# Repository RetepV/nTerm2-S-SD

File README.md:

# nTerm2-S-SD
My rendition of the uTerm2-S. In SMD, but easily solderable. In a slightly more usable form. As extra, it can switch between normal and cross (null-modem) in software.

This is a rendition of the nTerm2-S with extra PSRAM, a few extra I/O lines, and an SD card slot.

It is based on the FABGL library from Fabrizio Di Vittori.

THIS IS A WORK IN PROGESS! I.E. UNLESS STATED AS WORKING, IT DOES NOT WORK!

This design is available under GPL License V3. This means that I DO NOT release it for commercial use, unless with my explicit written and signed consent. Please contact me if you have commercial questions.

uTerm2-S: https://hackaday.io/project/181583-uterm2-s-a-multi-emulation-color-rs232-terminal
fabgl: http://www.fabglib.org/, https://github.com/fdivitto/FabGL

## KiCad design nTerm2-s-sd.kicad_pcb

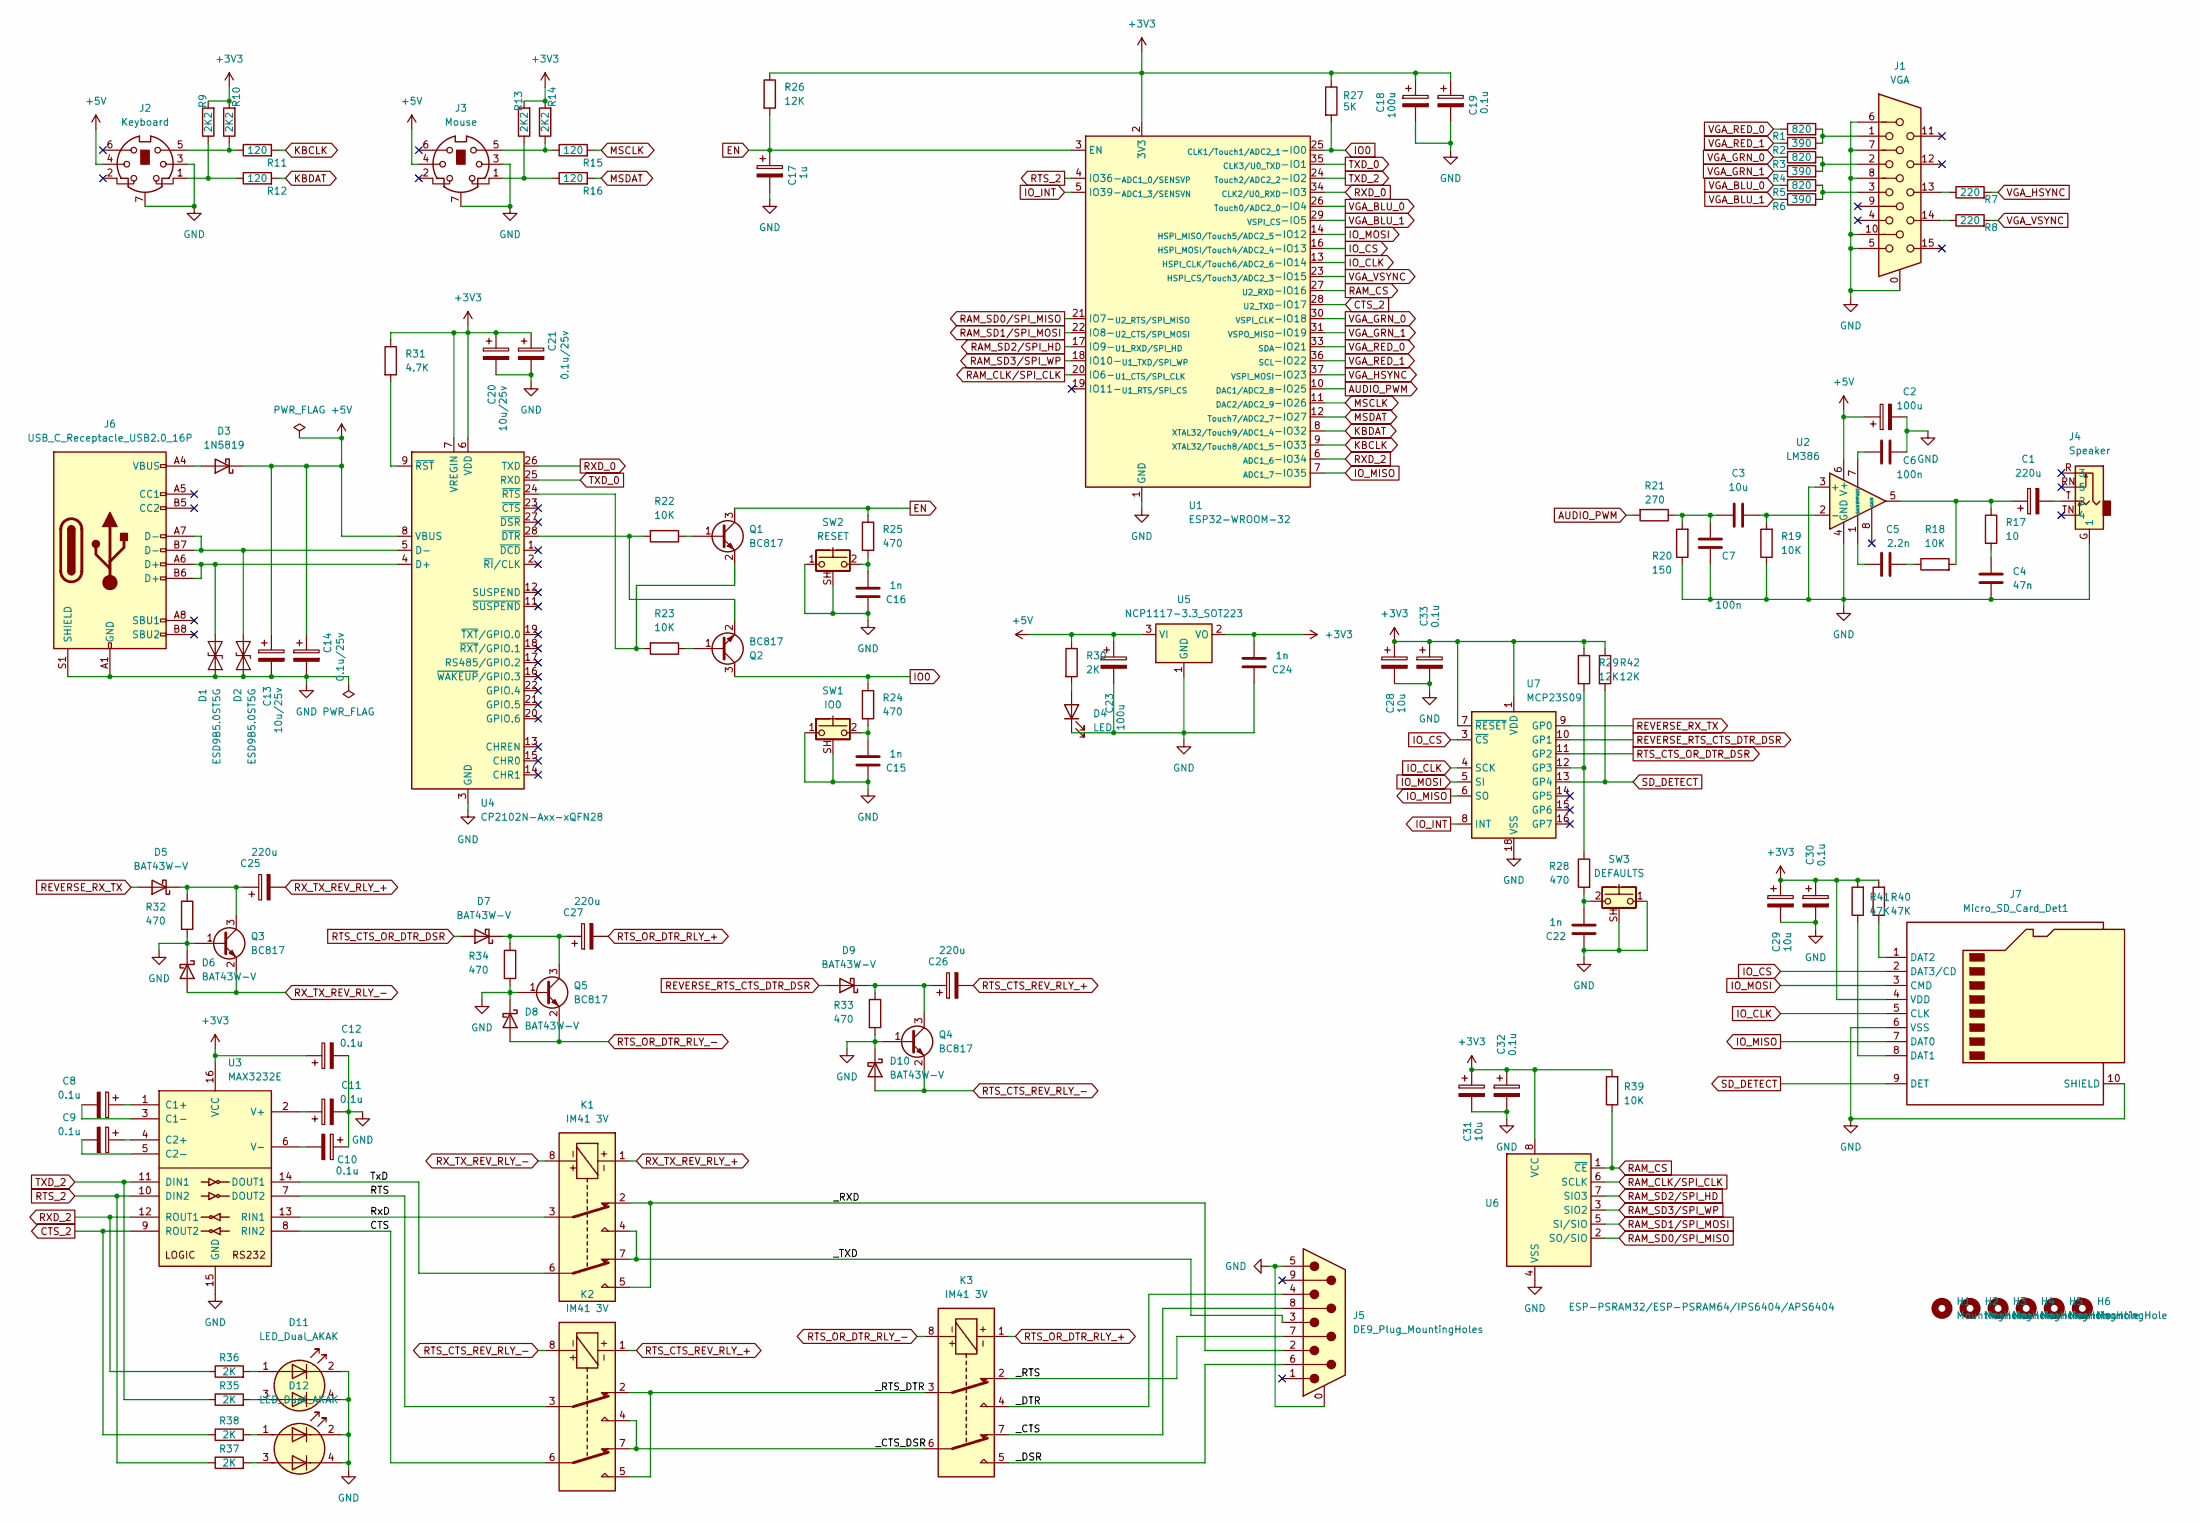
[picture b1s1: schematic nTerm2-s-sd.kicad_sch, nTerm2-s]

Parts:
C1: 220u; CP_Elec_6.3x7.7
C2: 100u; CP_Elec_6.3x7.7
C3: 10u; C_0805_2012Metric_Pad1.18x1.45mm_HandSolder
C4: 47n; C_0603_1608Metric_Pad1.08x0.95mm_HandSolder
C5: 2.2n; C_0603_1608Metric_Pad1.08x0.95mm_HandSolder
C6, C7: 100n; C_0603_1608Metric_Pad1.08x0.95mm_HandSolder
C8, C9, C10, C11, C12, C19, C30, C32, C33: 0.1u; CP_EIA-3216-18_Kemet-A_Pad1.58x1.35mm_HandSolder
C13, C20: 10u/25v; CP_EIA-3216-18_Kemet-A_Pad1.58x1.35mm_HandSolder
C14, C21: 0.1u/25v; CP_EIA-3216-18_Kemet-A_Pad1.58x1.35mm_HandSolder
C15, C16, C22, C24: 1n; C_0603_1608Metric_Pad1.08x0.95mm_HandSolder
C17: 1u; CP_EIA-3216-18_Kemet-A_Pad1.58x1.35mm_HandSolder
C18, C23: 100u; CP_EIA-3216-18_Kemet-A_Pad1.58x1.35mm_HandSolder
C25, C26, C27: 220u; CP_EIA-3216-18_Kemet-A_Pad1.58x1.35mm_HandSolder
C28, C29, C31: 10u; CP_EIA-3216-18_Kemet-A_Pad1.58x1.35mm_HandSolder
D1, D2: ESD9B5.0ST5G; D_SOD-923
D3: 1N5819; Nexperia_CFP3_SOD-123W
D4: LED; DIALIGHT_LED_3MM_SINGLE
D5, D6, D7, D8, D9, D10: BAT43W-V; D_SOD-123
D11, D12: LED_Dual_AKAK; DIALIGHT_LED_3MM_DOUBLE
H1, H2, H3, H4, H5, H6: MountingHole; MountingHole_3.2mm_M3
J1: VGA; DSUB-15-HD_Female_Horizontal_P2.29x1.98mm_EdgePinOffset8.35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
J2: Keyboard; Connector_Mini-DIN_Female_6Pin_2rows
J3: Mouse; Connector_Mini-DIN_Female_6Pin_2rows
J4: Speaker; Jack_3.5mm_Ledino_KB3SPRS_Horizontal
J5: DE9_Plug_MountingHoles; DSUB-9_Male_Horizontal_P2.77x2.84mm_EdgePinOffset4.94mm_Hou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
J6: USB_C_Receptacle_USB2.0_16P; USB_C_Receptacle_Molex_213716-0001
J7: Micro_SD_Card_Det1; GCT-MEM2055-00-190-01-A
K1, K2, K3: IM41 3V; Relay_DPDT_AXICOM_IMSeries_JLeg
Q1, Q2, Q3, Q4, Q5: BC817; SOT-23
R1, R3, R5: 820; R_0603_1608Metric_Pad0.98x0.95mm_HandSolder
R2, R4, R6: 390; R_0603_1608Metric_Pad0.98x0.95mm_HandSolder
R7, R8: 220; R_0603_1608Metric_Pad0.98x0.95mm_HandSolder
R9, R10, R13, R14: 2K2; R_0603_1608Metric_Pad0.98x0.95mm_HandSolder
R11, R12, R15, R16: 120; R_0603_1608Metric_Pad0.98x0.95mm_HandSolder
R17: 10; R_0603_1608Metric_Pad0.98x0.95mm_HandSolder
R18, R19, R22, R23, R39: 10K; R_0603_1608Metric_Pad0.98x0.95mm_HandSolder
R20: 150; R_0603_1608Metric_Pad0.98x0.95mm_HandSolder
R21: 270; R_0603_1608Metric_Pad0.98x0.95mm_HandSolder
R24, R25, R28, R32, R33, R34: 470; R_0603_1608Metric_Pad0.98x0.95mm_HandSolder
R26, R29, R42: 12K; R_0603_1608Metric_Pad0.98x0.95mm_HandSolder
R27: 5K; R_0603_1608Metric_Pad0.98x0.95mm_HandSolder
R30, R35, R36, R37, R38: 2K; R_0603_1608Metric_Pad0.98x0.95mm_HandSolder
R31: 4.7K; R_0603_1608Metric_Pad0.98x0.95mm_HandSolder
R40, R41: 47K; R_0603_1608Metric_Pad0.98x0.95mm_HandSolder
SW1: IO0; SW_Tactile_SPST_Angled_PTS645Vx58-2LFS
SW2: RESET; SW_Tactile_SPST_Angled_PTS645Vx58-2LFS
SW3: DEFAULTS; SW_Tactile_SPST_Angled_PTS645Vx58-2LFS
U1: ESP32-WROOM-32
U2: LM386; SOIC-8_3.9x4.9mm_P1.27mm
U3: MAX3232E; SOIC-16_3.9x9.9mm_P1.27mm
U4: CP2102N-Axx-xQFN28; QFN-28-1EP_5x5mm_P0.5mm_EP3.35x3.35mm
U5: NCP1117-3.3_SOT223; SOT-223-3_TabPin2
U6: ESP-PSRAM32/ESP-PSRAM64/IPS6404/APS6404; SOIC-8_3.9x4.9mm_P1.27mm
U7: MCP23S09; SOIC-18W_7.5x11.6mm_P1.27mm

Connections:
+3V3: C12.1, C18.1, C19.1, C20.1, C21.1, C24.1, C28.1, C29.1, C30.1, C31.1, C32.1, C33.1, J7.4 (VDD), R9.2, R10.2, R13.2, R14.2, R26.1, R27.1, R29.1, R31.1, R39.2, R40.2, R41.2, R42.1, U1.2 (3V3), U3.16 (VCC), U4.6 (VDD), U4.7 (VREGIN), U5.2 (VO), U6.8 (VCC), U7.1 (VDD), U7.7 (~RESET)
+5V: C2.1, C13.1, C14.1, C23.1, D3.1 (K), J2.4, J3.4, R30.1, U2.6 (V+), U4.8 (VBUS), U5.3 (VI)
/CTS: K2.6, U3.8 (RIN2)
/RTS: K2.3, U3.7 (DOUT2)
/RxD: K1.3, U3.13 (RIN1)
/TxD: K1.6, U3.14 (DOUT1)
/_CTS: J5.8, K3.7
/_CTS_DSR: K2.4, K2.7, K3.6
/_DSR: J5.6, K3.5
/_DTR: J5.4, K3.4
/_RTS: J5.7, K3.2
/_RTS_DTR: K2.2, K2.5, K3.3
/_RXD: J5.2, K1.2, K1.5
/_TXD: J5.3, K1.4, K1.7
AUDIO_PWM: R21.2, U1.10 (_{DAC1/ADC2_8}-IO25)
CTS_2: R38.1, U1.28 (_{U2_TXD}-IO17), U3.9 (ROUT2)
EN: C17.1, Q1.3 (C), R25.1, R26.2, U1.3 (EN)
GND: C2.2, C4.2, C6.2, C7.1, C10.1, C11.2, C12.2, C13.2, C14.2, C15.2, C16.2, C17.2, C18.2, C19.2, C20.2, C21.2, C22.2, C23.2, C24.2, C28.2, C29.2, C30.2, C31.2, C32.2, C33.2, D1.1 (A1), D2.1 (A1), D4.2 (K), D6.1 (K), D8.1 (K), D10.1 (K), D11.2 (K1), D11.4 (K2), D12.2 (K1), D12.4 (K2), J1.0, J1.5, J1.6, J1.7, J1.8, J1.10, J2.3, J2.7, J3.3, J3.7, J4.G (1), J5.0 (PAD), J5.5, J6.A1 (GND), J6.A12 (GND), J6.B1 (GND), J6.B12 (GND), J6.S1 (SHIELD), J7.6 (VSS), J7.10 (SHIELD), Q3.1 (B), Q4.1 (B), Q5.1 (B), R19.1, R20.1, R32.2, R33.2, R34.2, SW1.1, SW1.SH (B), SW2.1, SW2.SH (B), SW3.1, SW3.SH (B), U1.1 (GND), U1.15 (GND), U1.38 (GND), U1.39 (GND), U2.3 (+), U2.4 (GND), U3.15 (GND), U4.3 (GND), U4.29 (GND), U5.1 (GND), U6.4 (VSS), U7.18 (VSS)
IO0: Q2.3 (C), R24.1, R27.2, U1.25 (_{CLK1/Touch1/ADC2_1}-IO0)
IO_CLK: J7.5 (CLK), U1.13 (_{HSPI_CLK/Touch6/ADC2_6}-IO14), U7.4 (SCK)
IO_CS: J7.2 (DAT3/CD), U1.16 (_{HSPI_MOSI/Touch4/ADC2_4}-IO13), U7.3 (~CS)
IO_INT: U1.5 (IO39-_{ADC1_3/SENSVN}), U7.8 (INT)
IO_MISO: J7.7 (DAT0), U1.7 (_{ADC1_7}-IO35), U7.6 (SO)
IO_MOSI: J7.3 (CMD), U1.14 (_{HSPI_MISO/Touch5/ADC2_5}-IO12), U7.5 (SI)
KBCLK: R11.2, U1.9 (_{XTAL32/Touch8/ADC1_5}-IO33)
KBDAT: R12.2, U1.8 (_{XTAL32/Touch9/ADC1_4}-IO32)
MSCLK: R15.2, U1.11 (_{DAC2/ADC2_9}-IO26)
MSDAT: R16.2, U1.12 (_{Touch7/ADC2_7}-IO27)
unnamed: C1.1, R17.1, R18.2, U2.5
unnamed: C3.1, C7.2, R20.2, R21.1
unnamed: C4.1, R17.2
unnamed: C5.1, U2.1 (GAIN)
unnamed: C5.2, R18.1
unnamed: C15.1, R24.2, SW1.2
unnamed: C16.1, R25.2, SW2.2
unnamed: C22.1, R28.2, SW3.2
unnamed: D1.2 (A2), J6.A6 (D+), J6.B6 (D+), U4.4 (D+)
unnamed: D2.2 (A2), J6.A7 (D-), J6.B7 (D-), U4.5 (D-)
unnamed: D3.2 (A), J6.A4 (VBUS), J6.A9 (VBUS), J6.B4 (VBUS), J6.B9 (VBUS)
unnamed: D4.1 (A), R30.2
unnamed: C25.1, D5.1 (K), Q3.3 (C), R32.1
unnamed: C27.1, D7.1 (K), Q5.3 (C), R34.1
unnamed: C26.1, D9.1 (K), Q4.3 (C), R33.1
unnamed: D11.1 (A1), R36.2
unnamed: D11.3 (A2), R35.2
unnamed: D12.1 (A1), R38.2
unnamed: D12.3 (A2), R37.2
unnamed: J1.1, R1.2, R2.2
unnamed: J1.2, R3.2, R4.2
unnamed: J1.3, R5.2, R6.2
unnamed: J1.13, R7.1
unnamed: J1.14, R8.1
unnamed: J2.1, R9.1, R12.1
unnamed: J2.5, R10.1, R11.1
unnamed: J3.1, R13.1, R16.1
unnamed: J3.5, R14.1, R15.1
unnamed: C1.2, J4.T (2)
unnamed: J7.8 (DAT1), R41.1
unnamed: J7.1 (DAT2), R40.1
unnamed: Q1.1 (B), R22.1
unnamed: Q1.2 (E), R23.2, U4.24 (~RTS)
unnamed: Q2.1 (B), R23.1
unnamed: Q2.2 (E), R22.2, U4.28 (~DTR)
unnamed: C3.2, R19.2, U2.2 (-)
unnamed: C6.1, U2.7 (BYPASS)
unnamed: C8.1, U3.1 (C1+)
unnamed: C8.2, U3.3 (C1-)
unnamed: C9.1, U3.4 (C2+)
unnamed: C9.2, U3.5 (C2-)
unnamed: C11.1, U3.2 (V+)
unnamed: C10.2, U3.6 (V-)
unnamed: R31.2, U4.9 (~RST)
unnamed: R28.1, R29.2, U7.12 (GP3)
RAM_CLK/SPI_CLK: U1.20 (IO6-_{U1_CTS/SPI_CLK}), U6.6 (SCLK)
RAM_CS: R39.1, U1.27 (_{U2_RXD}-IO16), U6.1 (~CE)
RAM_SD0/SPI_MISO: U1.21 (IO7-_{U2_RTS/SPI_MISO}), U6.2 (SO/SIO)
RAM_SD1/SPI_MOSI: U1.22 (IO8-_{U2_CTS/SPI_MOSI}), U6.5 (SI/SIO)
RAM_SD2/SPI_HD: U1.17 (IO9-_{U1_RXD/SPI_HD}), U6.7 (SIO3)
RAM_SD3/SPI_WP: U1.18 (IO10-_{U1_TXD/SPI_WP}), U6.3 (SIO2)
REVERSE_RTS_CTS_DTR_DSR: D9.2 (A), U7.10 (GP1)
REVERSE_RX_TX: D5.2 (A), U7.9 (GP0)
RTS_2: R37.1, U1.4 (IO36-_{ADC1_0/SENSVP}), U3.10 (DIN2)
RTS_CTS_OR_DTR_DSR: D7.2 (A), U7.11 (GP2)
RTS_CTS_REV_RLY_+: C26.2, K2.1
RTS_CTS_REV_RLY_-: D10.2 (A), K2.8, Q4.2 (E)
RTS_OR_DTR_RLY_+: C27.2, K3.1
RTS_OR_DTR_RLY_-: D8.2 (A), K3.8, Q5.2 (E)
RXD_0: U1.34 (_{CLK2/U0_RXD}-IO3), U4.26 (TXD)
RXD_2: R36.1, U1.6 (_{ADC1_6}-IO34), U3.12 (ROUT1)
RX_TX_REV_RLY_+: C25.2, K1.1
RX_TX_REV_RLY_-: D6.2 (A), K1.8, Q3.2 (E)
SD_DETECT: J7.9 (DET), R42.2, U7.13 (GP4)
TXD_0: U1.35 (_{CLK3/U0_TXD}-IO1), U4.25 (RXD)
TXD_2: R35.1, U1.24 (_{Touch2/ADC2_2}-IO2), U3.11 (DIN1)
VGA_BLU_0: R5.1, U1.26 (_{Touch0/ADC2_0}-IO4)
VGA_BLU_1: R6.1, U1.29 (_{VSPI_CS}-IO5)
VGA_GRN_0: R3.1, U1.30 (_{VSPI_CLK}-IO18)
VGA_GRN_1: R4.1, U1.31 (_{VSPO_MISO}-IO19)
VGA_HSYNC: R7.2, U1.37 (_{VSPI_MOSI}-IO23)
VGA_RED_0: R1.1, U1.33 (_{SDA}-IO21)
VGA_RED_1: R2.1, U1.36 (_{SCL}-IO22)
VGA_VSYNC: R8.2, U1.23 (_{HSPI_CS/Touch3/ADC2_3}-IO15)

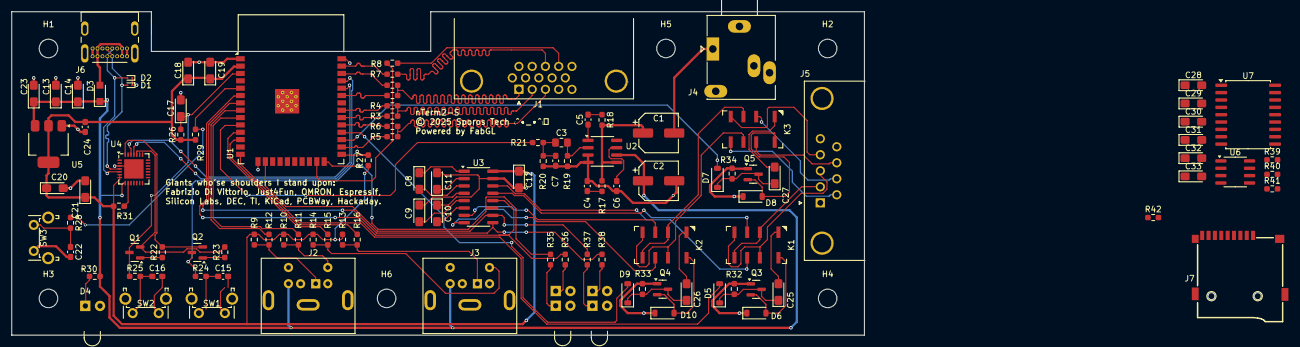
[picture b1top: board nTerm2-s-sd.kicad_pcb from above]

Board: 2 copper layers, 147.3 x 55.9 mm, 118 parts (0 on the bottom side), 102 nets.

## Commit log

2025-01-20 Backup
2025-01-24 If we move the DFLT button to the GPIO extender, we can use the input for the INT signal. And if we connected the SD DETECT output to the GPIO extender, we can detect card changes. And we still have 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

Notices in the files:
nTerm2-s-sd.kicad_pcb:
© 2025 Sporos Tech ₍^•_•^₎ﾉ
